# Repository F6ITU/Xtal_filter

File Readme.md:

A simple 4th order 10 MHz xtal filter for Grehack 2018 Workshop

A Kicad project for GreHack 2018 workshop

This repository contains a easy to build-easy to reproduce 4th order filter using low cost 10 MHz crystal device in HC49 form factor.

This filter has been designed for educational purpose, and could be the perfect companion for a 10 MHz harmonic-free reference clock 
(gps-do, ocxo or any kind of digitaly generated square wave RF source)

This filter could be used in conjunction with the OCXO based "Aion" reference clock 

https://github.com/F6ITU/OCXO

This board has been designed with Kicad, an Open Source EDA software developped by the CERN.

For better performances, noise imunity and port isolation, this board should be shielded. 

The "Simu" subdirectory contains several simulation and measurement files : 
* 10M-4-5kHz 337ohms 47pf.sch is the "ADDE Filter design" simulation file and schematics of the filter itself
* BOM.doc is the Bill of Material used during the Grehack 2018 workshop
* filtre 10 MHz 4 eme ordre2.png is a screen capture of the filter's response measured with a Network Analyzer (Smith chart and amplitude/insertion losses) 
* filtre 10 MHz 4eme ordre.s2p is the real characteristic of the filter (2 port Touchstone file format). This file could be 
imported in any kind or analyzer or RF simulation software (QUCS, Elsie, VNWA.exe etc)
* filtre.jpg is a picture of the filter itself, without shield

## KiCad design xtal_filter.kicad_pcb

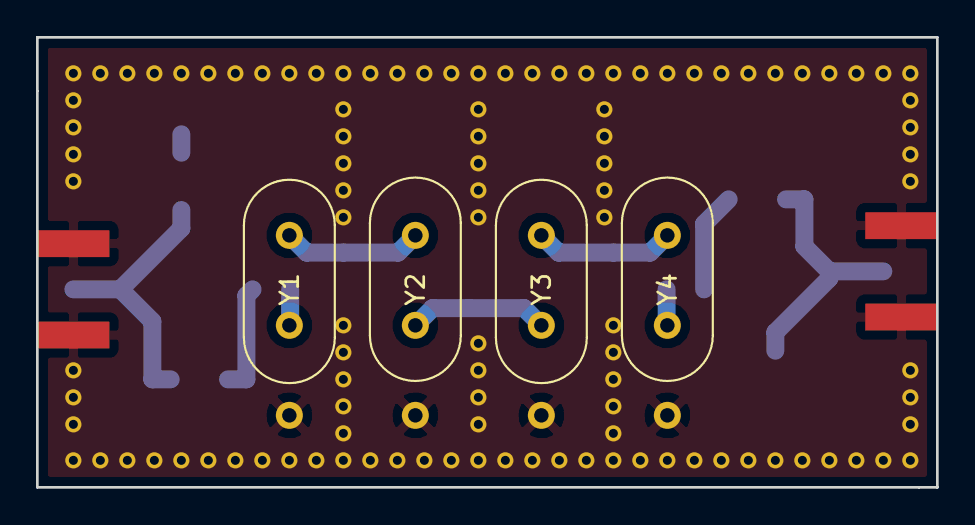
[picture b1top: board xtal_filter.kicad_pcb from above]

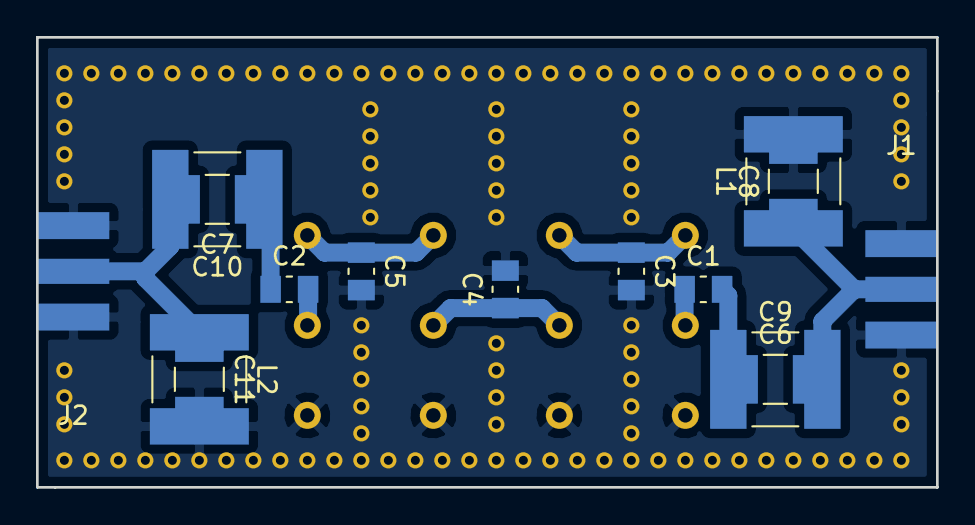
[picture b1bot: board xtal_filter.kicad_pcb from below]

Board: 2 copper layers, 50.0 x 25.0 mm, 19 parts (15 on the bottom side), 10 nets.

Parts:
C1, C2, C3, C4, C5: C_Small; C_0805_2012Metric_Pad1.15x1.50mm_HandSolder
C6, C7, C8, C11: C_Small; C_1210_3225Metric_Pad1.24x2.70mm_HandSolder
C9, C10: C_Small; C_2220_5650Metric_Pad2.02x5.50mm_HandSolder
J1, J2: Conn_Coaxial; SMA_EDGE_NRW
L1, L2: L_Small; C_2220_5650Metric_Pad2.02x5.50mm_HandSolder
Y1, Y2, Y3, Y4: 10M; Crystal_HC49-U-3Pin_Vertical

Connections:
GND: C3.2, C4.2, C5.2, C8.2, C11.2, J1.2, J2.2, L1.2, L2.2, Y1.3, Y2.3, Y3.3, Y4.3
unnamed: C1.1, Y1.1
unnamed: C1.2, C6.1, C9.1
unnamed: C2.2, Y4.2
unnamed: C3.1, Y1.2, Y2.1
unnamed: C4.1, Y2.2, Y3.1
unnamed: C5.1, Y3.2, Y4.1
unnamed: C6.2, C8.1, C9.2, J1.1, L1.1
unnamed: C2.1, C7.1, C10.1
unnamed: C7.2, C10.2, C11.1, J2.1, L2.1

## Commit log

2018-11-12 xtal filter firste commit
